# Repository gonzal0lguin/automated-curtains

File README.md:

# automated-curtains

Motorized roller blinds controlled by an ESP32: a NEMA 17 stepper with a
TMC2209 driver, an AS5600 magnetic encoder for absolute position, and a
smart-knob style controller (rotary encoder and GC9A01 round display). It also
has a web app and API, so an iPhone Shortcut can open the blinds when the alarm
goes off.

- Project idea and goals: [idea.md](idea.md)
- Firmware, wiring, setup, API and testing: [firmware/README.md](firmware/README.md)

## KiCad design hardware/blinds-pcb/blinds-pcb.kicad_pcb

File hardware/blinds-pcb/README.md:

# Smart Blinds — control panel PCB

KiCad 10 project for the wall control panel of the motorized blind: a round
board that carries the ESP32, the stepper driver, the ring knob, the LED ring
and the connectors for the round display and the motor.

**Status: schematic complete** (ERC clean, [`doc/schematic.pdf`](doc/schematic.pdf)).
PCB layout is the next phase; the board file still holds an old, partial placement.

## What is on the board

| Block | Part |
|---|---|
| Controller | ESP32 NodeMCU 38-pin, in sockets |
| Motor driver | BigTreeTech TMC2209 module, in sockets |
| Knob | ALPS EC35A1520402 ring encoder + centre tact switch |
| Lights | 10 × WS2812B with a 5 V level shifter |
| Power | 12 V barrel jack, fuse, reverse-polarity and surge protection, 5 V 2 A buck (AP63205) |
| Display | Connector for a GC9A01 1.28" round LCD module |
| Motor link | RJ45 to the NEMA 17 and its AS5600 encoder (**not Ethernet**) |
| Extras | Ambient light sensor, 12 V sense, RESET/BOOT buttons, spare I2C header |

## Documents

| File | Contents |
|---|---|
| [`doc/hardware-design.md`](doc/hardware-design.md) | Every circuit block explained: what it does, why each value, what to check |
| [`doc/pinmap.md`](doc/pinmap.md) | ESP32 pin map, connector pinouts, firmware edits for the PCB |
| [`doc/bom.md`](doc/bom.md) | Parts list with packages and LCSC numbers |
| [`doc/schematic.pdf`](doc/schematic.pdf) | Printable schematic |
| [`doc/PLAN.md`](doc/PLAN.md) | Working plan, decisions and log |
| [`tools/gen_schematic/`](tools/gen_schematic/) | Script that generated the schematic and checks its netlist. **Re-running it overwrites edits made in KiCad** |
| [`doc/Curtain control panel hardware design.pdf`](doc/Curtain%20control%20panel%20hardware%20design.pdf) | Earlier design study, including the press-the-screen mechanism |
| [`../../firmware/README.md`](../../firmware/README.md) | Firmware: build, flash, test firmwares, API |

## Opening the project

Open `blinds-pcb.kicad_pro` with KiCad 10 or newer. Project-specific symbols,
footprints and 3D models are in `lib/` (`blinds.kicad_sym`, `blinds.pretty/`,
`3d/`) and are found through `${KIPRJMOD}`, so no global library setup is needed.

## Things to know before powering it

- **Supply:** 12 V DC, 2 A, centre-positive, 5.5 mm barrel plug.
- **The RJ45 port carries 12 V motor current.** Never connect it to a
  computer, router or switch, and never unplug it while the board is powered.
- **Motor current** is set by the firmware over UART; keep it at or below
  about 1 A RMS because it flows through the RJ45 cable.
- **USB and 12 V together are fine:** a diode stops USB from powering the
  LED ring or back-feeding the regulator. The NodeMCU itself has no diode on
  its USB 5 V, so do not leave it plugged into a computer that is switched
  off while the 12 V adapter is on.
- **Flashing:** plug USB into the NodeMCU while it sits in the board. If
  automatic download mode fails, hold BOOT, tap RESET, release BOOT.
- **Firmware pins differ from the breadboard prototype.** Apply the edits
  listed in [`doc/pinmap.md`](doc/pinmap.md) before flashing a PCB build.

Assembly order and the bring-up checklist are at the end of
[`doc/hardware-design.md`](doc/hardware-design.md).

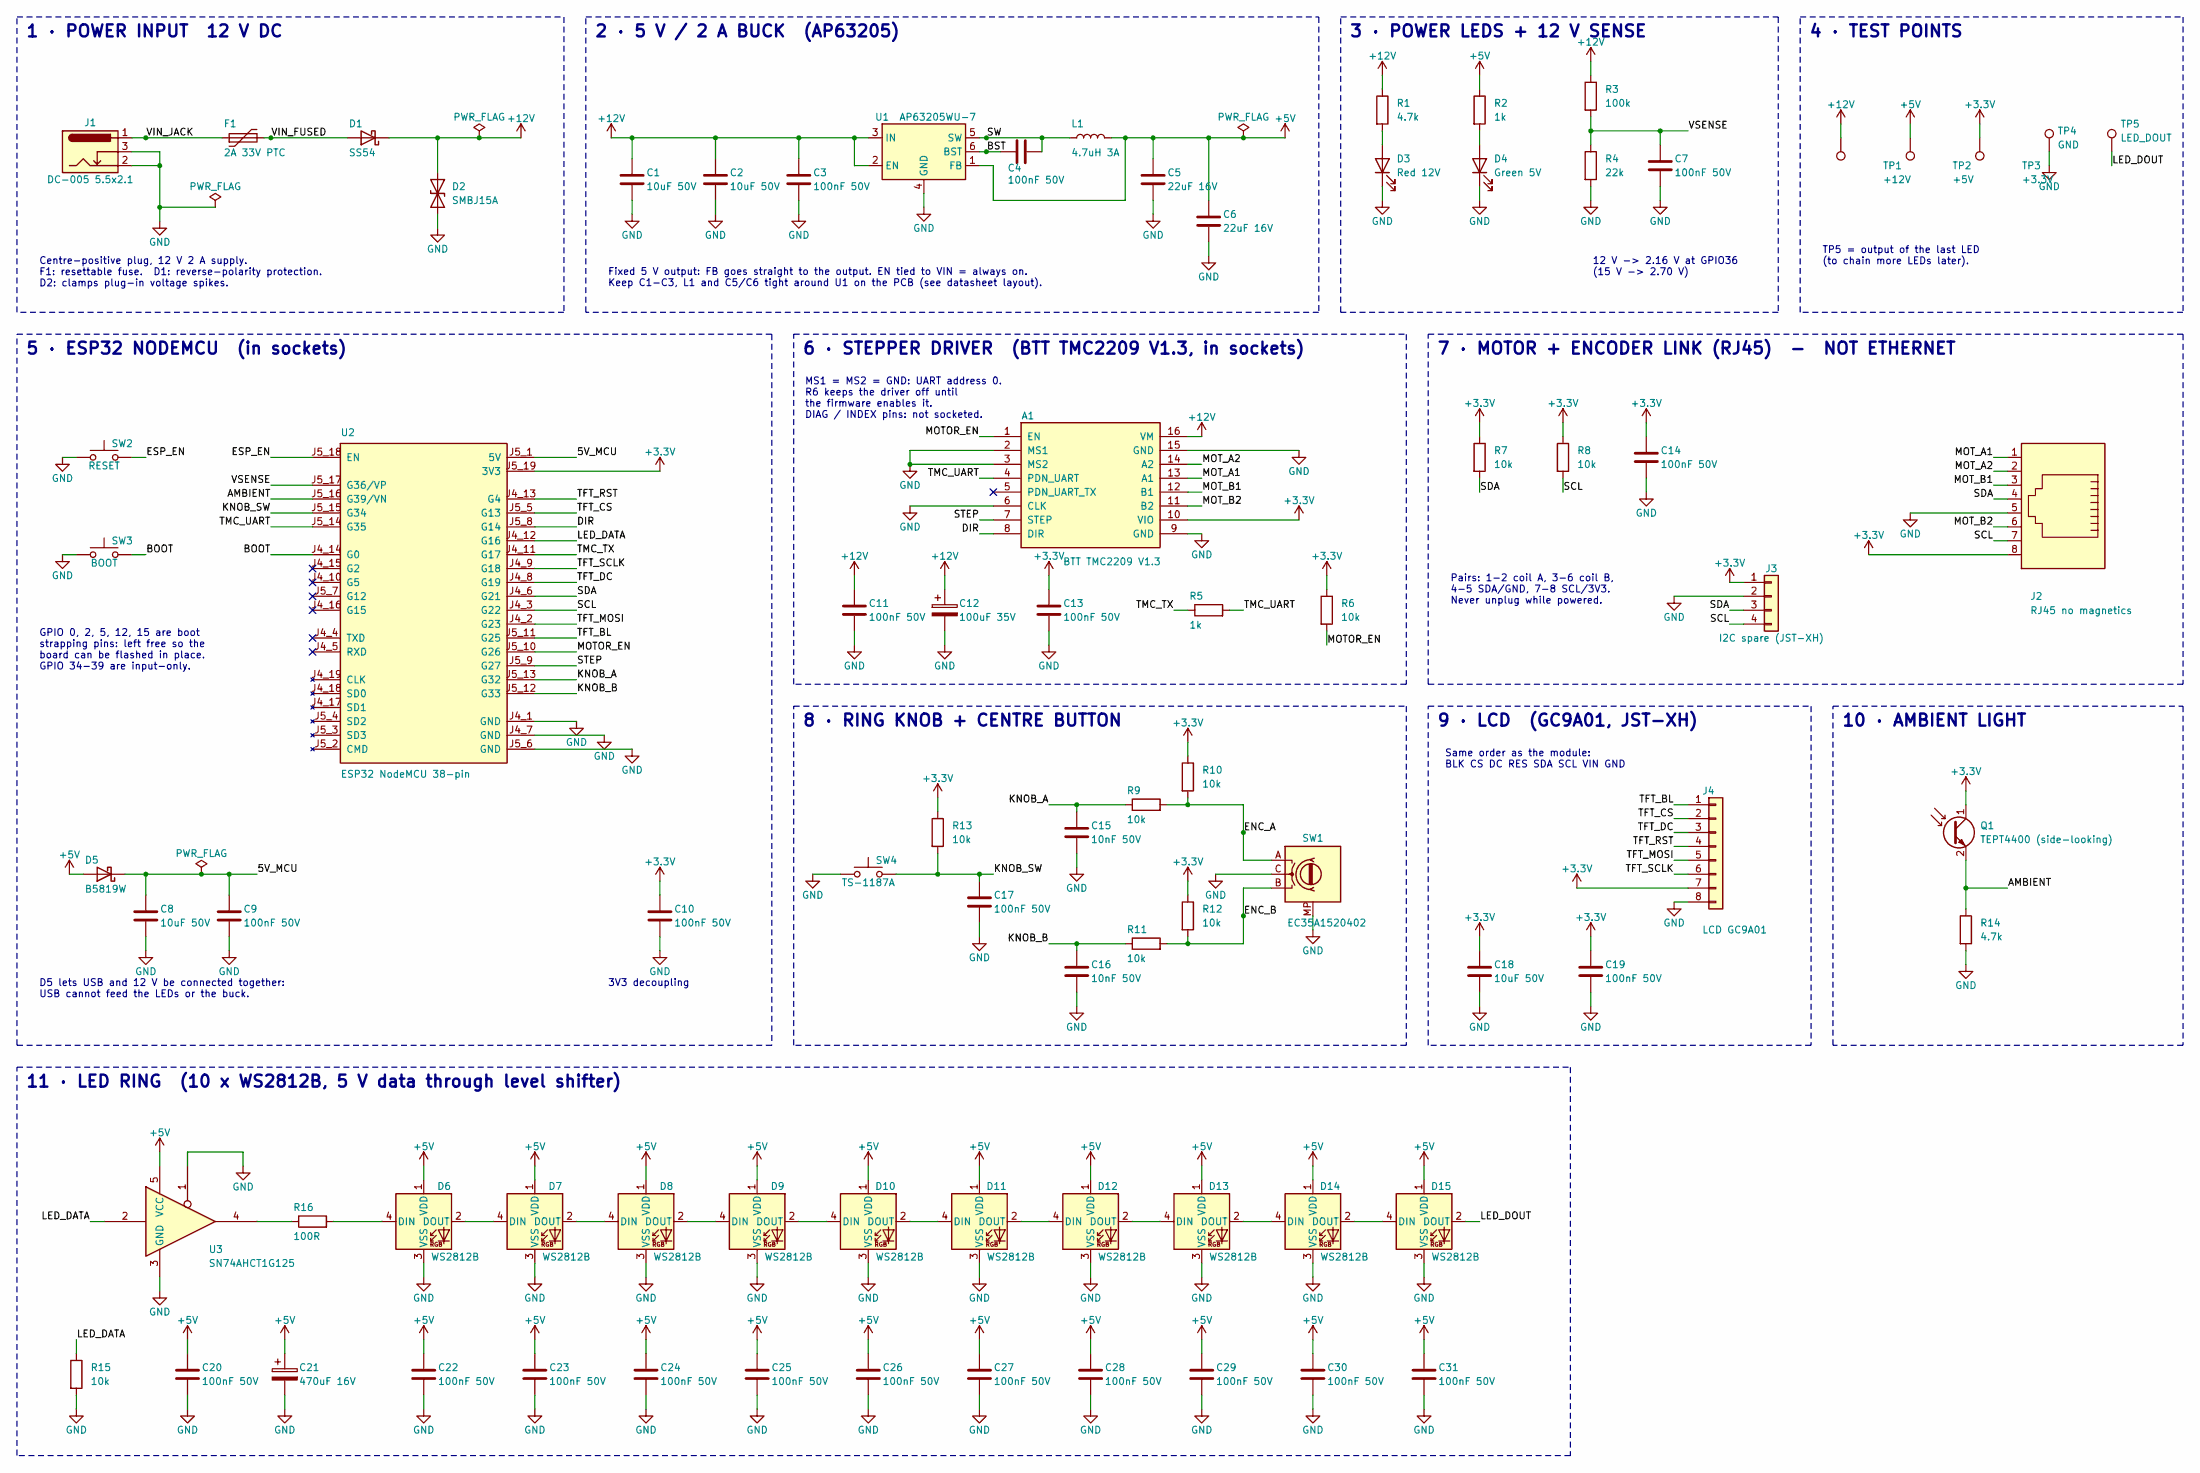
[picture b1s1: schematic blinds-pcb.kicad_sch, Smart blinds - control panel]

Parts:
A1: BTT TMC2209 V1.3; Pololu_Breakout-16_15.2x20.3mm
C1, C2, C8, C18: 10uF 50V; C_1206_3216Metric_Pad1.33x1.80mm_HandSolder; LCSC C13585
C3, C4, C7, C9, C10, C11, C13, C14, C17, C19, C20, C22, C23, C24, C25, C26, C27, C28, C29, C30, C31: 100nF 50V; C_0805_2012Metric_Pad1.18x1.45mm_HandSolder; LCSC C38141
C5, C6: 22uF 16V; C_0805_2012Metric_Pad1.18x1.45mm_HandSolder; LCSC C98190
C12: 100uF 35V; CP_Radial_D6.3mm_P2.50mm; LCSC C109392
C15, C16: 10nF 50V; C_0805_2012Metric_Pad1.18x1.45mm_HandSolder; LCSC C1710
C21: 470uF 16V; CP_Radial_D8.0mm_P3.50mm; LCSC C2943989
D1: SS54; D_SMA_Handsoldering; LCSC C7420369
D2: SMBJ15A; D_SMB_Handsoldering; LCSC C726824
D3: Red 12V; LED_0805_2012Metric_Pad1.15x1.40mm_HandSolder
D4: Green 5V; LED_0805_2012Metric_Pad1.15x1.40mm_HandSolder
D5: B5819W; D_SOD-123; LCSC C8598
D6, D7, D8, D9, D10, D11, D12, D13, D14, D15: WS2812B; LED_WS2812B_PLCC4_5.0x5.0mm_P3.2mm; LCSC C114588
F1: 2A 33V PTC; Fuse_1812_4532Metric_Pad1.30x3.40mm_HandSolder; LCSC C18198343
J1: DC-005 5.5x2.1; BarrelJack_Horizontal; LCSC C16214
J2: RJ45 no magnetics; RJ45_Amphenol_54602-x08_Horizontal; LCSC C2683359
J3: I2C spare (JST-XH); JST_XH_B4B-XH-A_1x04_P2.50mm_Vertical; LCSC C594232
J4: LCD GC9A01; JST_XH_B8B-XH-A_1x08_P2.50mm_Vertical; LCSC C10385
L1: 4.7uH 3A; L_Changjiang_FNR6045S; LCSC C168067
Q1: TEPT4400 (side-looking); LED_D3.0mm_Horizontal_O1.27mm_Z2.0mm_Clear; LCSC C132178
R1, R14: 4.7k; R_0805_2012Metric_Pad1.20x1.40mm_HandSolder; LCSC C17673
R2, R5: 1k; R_0805_2012Metric_Pad1.20x1.40mm_HandSolder; LCSC C17513
R3: 100k; R_0805_2012Metric_Pad1.20x1.40mm_HandSolder; LCSC C149504
R4: 22k; R_0805_2012Metric_Pad1.20x1.40mm_HandSolder
R6, R7, R8, R9, R10, R11, R12, R13, R15: 10k; R_0805_2012Metric_Pad1.20x1.40mm_HandSolder
R16: 100R; R_0805_2012Metric_Pad1.20x1.40mm_HandSolder
SW1: EC35A1520402; RotaryEncoder_Alps_EC35A1520402
SW2: RESET; SW_Tactile_SPST_Angled_PTS645Vx31-2LFS
SW3: BOOT; SW_Tactile_SPST_Angled_PTS645Vx31-2LFS
SW4: TS-1187A; SW_Push_1P1T_XKB_TS-1187A; LCSC C318889
TP1: +12V; TestPoint_Pad_D1.5mm
TP2: +5V; TestPoint_Pad_D1.5mm
TP3: +3.3V; TestPoint_Pad_D1.5mm
TP4: GND; TestPoint_Pad_D1.5mm
TP5: LED_DOUT; TestPoint_Pad_D1.5mm
U1: AP63205WU-7; TSOT-23-6_HandSoldering; LCSC C2071056
U2: ESP32 NodeMCU 38-pin; ESP32_NODEMCU
U3: SN74AHCT1G125; SOT-23-5_HandSoldering; LCSC C7484

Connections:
+3.3V: A1.10 (VIO), C10.1, C13.1, C14.1, C18.1, C19.1, J2.8, J3.1, J4.7, Q1.1 (C), R6.1, R7.1, R8.1, R10.1, R12.1, R13.1, TP3.1 (1_1), U2.J5_19 (3V3)
+5V: C5.1, C6.1, C20.1, C21.1, C22.1, C23.1, C24.1, C25.1, C26.1, C27.1, C28.1, C29.1, C30.1, C31.1, D5.2 (A), D6.1 (VDD), D7.1 (VDD), D8.1 (VDD), D9.1 (VDD), D10.1 (VDD), D11.1 (VDD), D12.1 (VDD), D13.1 (VDD), D14.1 (VDD), D15.1 (VDD), L1.2, R2.1, TP2.1 (1_1), U1.1 (FB), U3.5 (VCC)
+12V: A1.16 (VM), C1.1, C2.1, C3.1, C11.1, C12.1, D1.1 (K), D2.1 (A1), R1.1, R3.1, TP1.1 (1_1), U1.2 (EN), U1.3 (IN)
/5V_MCU: C8.1, C9.1, D5.1 (K), U2.J5_1 (5V)
/AMBIENT: Q1.2 (E), R14.1, U2.J5_16 (G39/VN)
/BOOT: SW3.2, U2.J4_14 (G0)
/BST: C4.1, U1.6 (BST)
/DIR: A1.8 (DIR), U2.J5_8 (G14)
/ENC_A: R9.2, R10.2, SW1.A
/ENC_B: R11.2, R12.2, SW1.B
/ESP_EN: SW2.2, U2.J5_18 (EN)
/KNOB_A: C15.1, R9.1, U2.J5_13 (G32)
/KNOB_B: C16.1, R11.1, U2.J5_12 (G33)
/KNOB_SW: C17.1, R13.2, SW4.2, U2.J5_15 (G34)
/LED_DATA: R15.1, U2.J4_12 (G16), U3.2
/LED_DOUT: D15.2 (DOUT), TP5.1 (1_1)
/MOTOR_EN: A1.1 (EN), R6.2, U2.J5_10 (G26)
/MOT_A1: A1.13 (A1), J2.1
/MOT_A2: A1.14 (A2), J2.2
/MOT_B1: A1.12 (B1), J2.3
/MOT_B2: A1.11 (B2), J2.6
/SCL: J2.7, J3.4, R8.2, U2.J4_3 (G22)
/SDA: J2.4, J3.3, R7.2, U2.J4_6 (G21)
/STEP: A1.7 (STEP), U2.J5_9 (G27)
/SW: C4.2, L1.1, U1.5 (SW)
/TFT_BL: J4.1, U2.J5_11 (G25)
/TFT_CS: J4.2, U2.J5_5 (G13)
/TFT_DC: J4.3, U2.J4_8 (G19)
/TFT_MOSI: J4.5, U2.J4_2 (G23)
/TFT_RST: J4.4, U2.J4_13 (G4)
/TFT_SCLK: J4.6, U2.J4_9 (G18)
/TMC_TX: R5.1, U2.J4_11 (G17)
/TMC_UART: A1.4 (PDN_UART), R5.2, U2.J5_14 (G35)
/VIN_FUSED: D1.2 (A), F1.2
/VIN_JACK: F1.1, J1.1
/VSENSE: C7.1, R3.2, R4.1, U2.J5_17 (G36/VP)
GND: A1.2 (MS1), A1.3 (MS2), A1.6 (CLK), A1.9 (GND), A1.15 (GND), C1.2, C2.2, C3.2, C5.2, C6.2, C7.2, C8.2, C9.2, C10.2, C11.2, C12.2, C13.2, C14.2, C15.2, C16.2, C17.2, C18.2, C19.2, C20.2, C21.2, C22.2, C23.2, C24.2, C25.2, C26.2, C27.2, C28.2, C29.2, C30.2, C31.2, D2.2 (A2), D3.1 (K), D4.1 (K), D6.3 (VSS), D7.3 (VSS), D8.3 (VSS), D9.3 (VSS), D10.3 (VSS), D11.3 (VSS), D12.3 (VSS), D13.3 (VSS), D14.3 (VSS), D15.3 (VSS), J1.2, J1.3, J2.5, J3.2, J4.8, R4.2, R14.2, R15.2, SW1.C, SW1.MP, SW2.1, SW3.1, SW4.1, TP4.1 (1_1), U1.4 (GND), U2.J4_1 (GND), U2.J4_7 (GND), U2.J5_6 (GND), U3.1, U3.3 (GND)
unnamed: D3.2 (A), R1.2
unnamed: D4.2 (A), R2.2
unnamed: D6.4 (DIN), R16.2
unnamed: D6.2 (DOUT), D7.4 (DIN)
unnamed: D7.2 (DOUT), D8.4 (DIN)
unnamed: D8.2 (DOUT), D9.4 (DIN)
unnamed: D9.2 (DOUT), D10.4 (DIN)
unnamed: D10.2 (DOUT), D11.4 (DIN)
unnamed: D11.2 (DOUT), D12.4 (DIN)
unnamed: D12.2 (DOUT), D13.4 (DIN)
unnamed: D13.2 (DOUT), D14.4 (DIN)
unnamed: D14.2 (DOUT), D15.4 (DIN)
unnamed: R16.1, U3.4

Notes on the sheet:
1 · POWER INPUT 12 V DC
Centre-positive plug, 12 V 2 A supply. F1: resettable fuse. D1: reverse-polarity protection. D2: clamps plug-in voltage spikes.
2 · 5 V / 2 A BUCK (AP63205)
Fixed 5 V output: FB goes straight to the output. EN tied to VIN = always on. Keep C1-C3, L1 and C5/C6 tight around U1 on the PCB (see datasheet layout).
3 · POWER LEDS + 12 V SENSE
12 V -> 2.16 V at GPIO36 (15 V -> 2.70 V)
4 · TEST POINTS
TP5 = output of the last LED (to chain more LEDs later).
5 · ESP32 NODEMCU (in sockets)
D5 lets USB and 12 V be connected together: USB cannot feed the LEDs or the buck.
3V3 decoupling
GPIO 0, 2, 5, 12, 15 are boot strapping pins: left free so the board can be flashed in place. GPIO 34-39 are input-only.
6 · STEPPER DRIVER (BTT TMC2209 V1.3, in sockets)
MS1 = MS2 = GND: UART address 0. R6 keeps the driver off until the firmware enables it. DIAG / INDEX pins: not socketed.
7 · MOTOR + ENCODER LINK (RJ45) - NOT ETHERNET
Pairs: 1-2 coil A, 3-6 coil B, 4-5 SDA/GND, 7-8 SCL/3V3. Never unplug while powered.
8 · RING KNOB + CENTRE BUTTON
9 · LCD (GC9A01, JST-XH)
Same order as the module: BLK CS DC RES SDA SCL VIN GND
10 · AMBIENT LIGHT
11 · LED RING (10 x WS2812B, 5 V data through level shifter)

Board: 2 copper layers, 87 parts (60 on the bottom side), 50 nets, no tracks yet.

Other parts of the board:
H1, H2, H3, H4: M3; MountingHole_3.2mm_M3
MECH1: Knob_Centre_Mechanics

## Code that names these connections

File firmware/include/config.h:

#pragma once
// =============================================================================
//  Hardware configuration — single source of truth for pins and constants.
//  Runtime-tunable values (speeds, brightness, calibration...) live in
//  Settings (lib/settings) and are editable from the knob menu / web UI.
// =============================================================================

// ---------------------------------------------------------------- AS5600 (I2C)
#define PIN_I2C_SDA 21
#define PIN_I2C_SCL 22
#define I2C_FREQ_HZ 400000

// ------------------------------------------------- Rotary encoder (EC11 knob)
#define PIN_KNOB_A  32
#define PIN_KNOB_B  33
#define PIN_KNOB_SW 13
// Quadrature transitions per mechanical detent. Most EC11 knobs are 4, some
// are 2. Run the `test-knob` firmware: it prints raw transitions per detent.
#define KNOB_TRANSITIONS_PER_DETENT 2

// ---------------------------------------------- TMC2209 stepper driver (STEP/DIR)
#define PIN_MOTOR_STEP 27
#define PIN_MOTOR_DIR  14
// WARNING: GPIO12 is a boot strapping pin (flash voltage). If your driver board
// pulls EN high, the ESP32 will not boot. If that happens move EN to GPIO26.
#define PIN_MOTOR_EN   12

// Optional TMC2209 UART (PDN_UART pin). Wire ESP TX -> 1k resistor -> PDN_UART
// and ESP RX -> PDN_UART. If not wired, the firmware falls back to standalone
// mode automatically (microsteps/current set by the driver's pins/pot).
#define PIN_TMC_RX 16
#define PIN_TMC_TX 17
#define TMC_ADDRESS 0        // MS1/MS2 low = address 0
#define TMC_R_SENSE 0.11f    // most TMC2209 modules use 0.11 ohm

// ------------------------------------------------- GC9A01 240x240 round display
#define PIN_TFT_SCLK 18
#define PIN_TFT_MOSI 23
#define PIN_TFT_CS   5
#define PIN_TFT_DC   19
#define PIN_TFT_RST  4
#define PIN_TFT_BL   25
#define TFT_SPI_HZ   40000000

// ----------------------------------------------------------------- Constants
#define DEVICE_NAME       "blinds"          // default hostname -> http://blinds.local
#define WIFI_SETUP_AP     "Blinds-Setup"    // captive portal SSID when no WiFi saved
#define ENCODER_CPR       4096              // AS5600 counts per revolution

#ifndef FW_VERSION
#define FW_VERSION "dev"
#endif

#ifndef SIMULATE_MECHANICS
#define SIMULATE_MECHANICS 0
#endif

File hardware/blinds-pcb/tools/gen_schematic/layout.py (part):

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  53.34, 38.1, '~VIN_JACK', '~VIN_FUSED', 'C18198343')
H('D1', 'Device:D_Schottky', 'SS54', 'Diode_SMD:D_SMA_Handsoldering', 76.2, 38.1, '~VIN_FUSED', '~+12V', 'C7420369', rot=180)
V('D2', 'Device:D_TVS', 'SMBJ15A', 'Diode_SMD:D_SMB_Handsoldering', 88.9, 48.26, '~+12V', 'GND', 'C726824', rot=270)
s.wire('J1.1', 'F1.1'); s.label('VIN_JACK', 35.56, 38.1)
s.wire('F1.2', 'D1.2'); s.label('VIN_FUSED', 58.42, 38.1)
s.wire('D1.1', (104.14, 38.1)); s.power('+12V', 104.14, 38.1); s.flag(96.52, 38.1)
s.wire((88.9, 38.1), 'D2.1')
s.wire('J1.3', (38.1, 40.64), (38.1, 43.18)); s.wire('J1.2', (38.1, 43.18), (38.1, 53.34)); s.power('GND', 38.1, 53.34)
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s.wire('U1.6', 'C4.1'); s.wire('C4.2', (199.39, 38.1))
H('L1', 'Device:L', '4.7uH 3A', 'Inductor_SMD:L_Changjiang_FNR6045S', 208.28, 38.1, '~SW', '~+5V', 'C168067')
s.wire('U1.5', 'L1.1'); s.label('SW', 189.23, 38.1)
s.label('BST', 189.23, 40.64)
s.wire('L1.2', (243.84, 38.1)); s.power('+5V', 243.84, 38.1); s.flag(236.22, 38.1)
for ref, x in (('C5', 220.98), ('C6', 229.87)):
    pass
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R('R4', '22k', 281.94 + X3, 43.18, '~VSENSE', 'GND')
C('C7', '100nF', 294.64 + X3, 43.18, '~VSENSE')
s.wire('R3.2', 'R4.1'); s.wire((281.94 + X3, 36.83), (299.72 + X3, 36.83)); s.wire((294.64 + X3, 36.83), 'C7.1')
s.label('VSENSE', 299.72 + X3, 36.83)
s.text('12 V -> 2.16 V at GPIO36\n(15 V -> 2.70 V)', 300, 60)

# ============ 4. TEST POINTS ============
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    s.wire(f'{rp}.2', (226.06, yrow))
    s.wire(f'{rs}.1', (200.66, yrow)); s.wire((205.74, yrow), f'{c}.1')
    s.label(f'KNOB_{n}', 200.66, yrow, left=True)
s.label('ENC_A', 236.22, 165.1); s.label('ENC_B', 236.22, 180.34)
s.add('SW4', 'Switch:SW_Push', 'TS-1187A', 'Button_Switch_SMD:SW_Push_1P1T_XKB_TS-1187A', 167.64, 172.72, 0,
      {1: ('GND', 5.08), 2: '~KNOB_SW'}, 'C318889')
R('R13', '10k', 180.34, 165.1, '+3V3', '~KNOB_SW'); s.wire('R13.2', (180.34, 172.72))
C('C17', '100nF', 187.96, 177.8, '~KNOB_SW'); s.wire((187.96, 172.72), 'C17.1')
s.wire('SW4.2', (190.5, 172.72)); s.label('KNOB_SW', 190.5, 172.72)

# ============ 9. LCD ============
s.box(270, 142, 340, 204, '9 · LCD  (GC9A01, JST-XH)')
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s.add('Q1', 'Sensor_Optical:TEPT4400', 'TEPT4400 (side-looking)', 'LED_THT:LED_D3.0mm_Horizontal_O1.27mm_Z2.0mm_Clear', 365.76, 165.1, 0,
      {1: '+3V3', 2: '~AMBIENT'}, 'C132178')
R('R14', '4.7k', 368.3, 182.88, '~AMBIENT', 'GND')
s.wire('Q1.2', 'R14.1'); s.wire((368.3, 175.26), (375.92, 175.26)); s.label('AMBIENT', 375.92, 175.26)

# ============ 11. LED RING ============
s.box(12, 208, 296, 279, '11 · LED RING  (10 x WS2812B, 5 V data through level shifter)')
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
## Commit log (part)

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2022-11-09 Edit gitignore
2025-11-09 Create PIO project with ESP32 webtemplate
